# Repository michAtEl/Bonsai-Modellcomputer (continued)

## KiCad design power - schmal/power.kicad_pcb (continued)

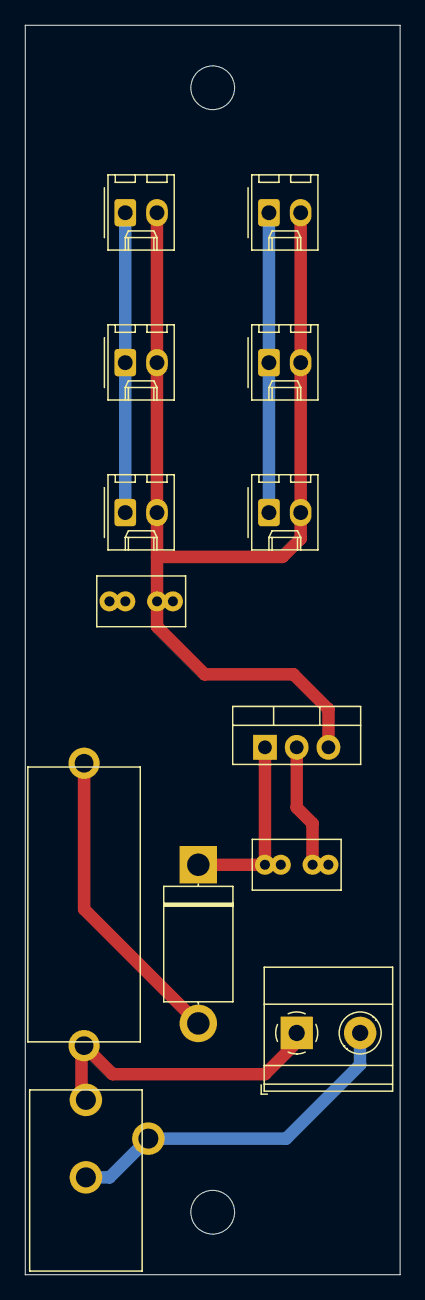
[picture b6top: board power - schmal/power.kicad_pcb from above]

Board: 2 copper layers, 30.0 x 100.0 mm, 15 parts (0 on the bottom side), 5 nets.

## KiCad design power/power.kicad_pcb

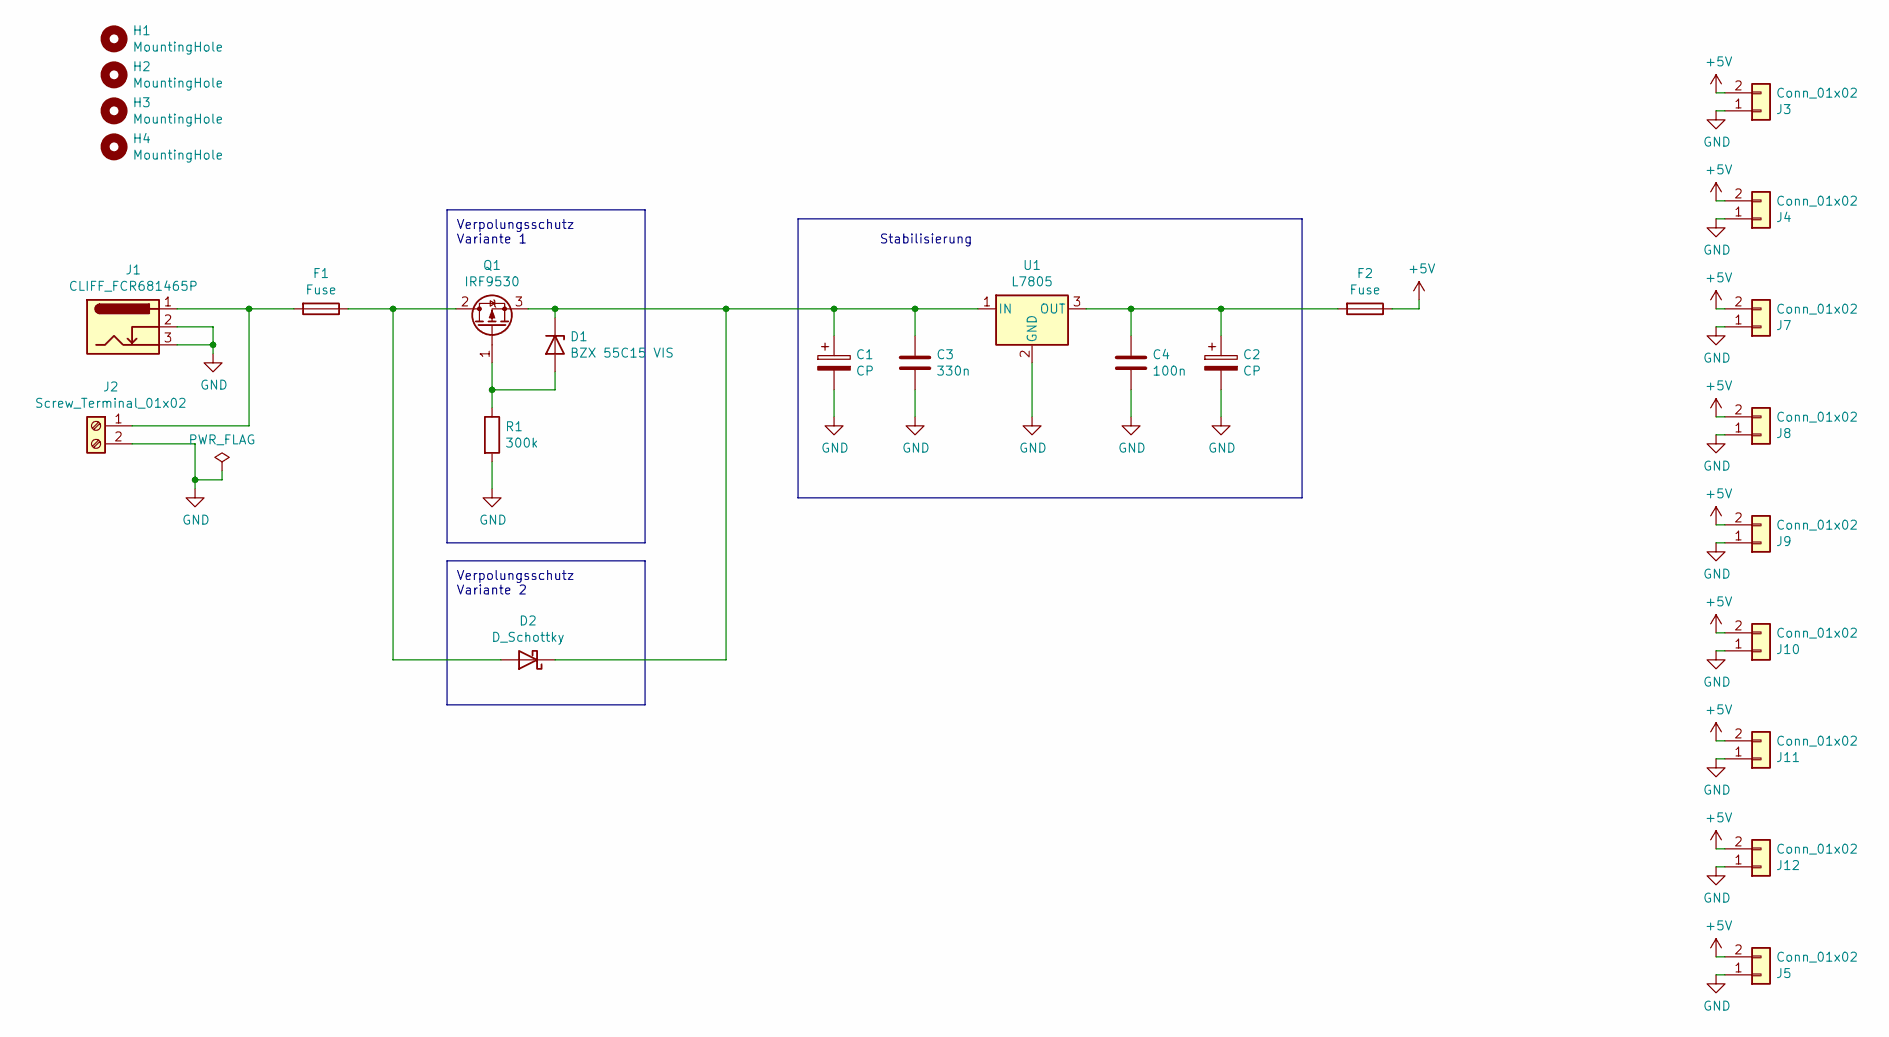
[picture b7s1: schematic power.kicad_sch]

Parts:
C1, C2: CP; CP_2.5_3.5_5
C3: 330n; C_Rect_L7.2mm_W2.2mm_P2.54mm_P5.08mm
C4: 100n; C_Rect_L7.2mm_W2.2mm_P2.54mm_P5.08mm
D1: BZX 55C15 VIS; D_T-1_P10.16mm_Horizontal
D2: D_Schottky; D_DO-201AE_P12.70mm_Horizontal
F1, F2: Fuse; Sicherungshalter
H1, H2, H3, H4: MountingHole; MountingHole_3.5mm
J1: CLIFF_FCR681465P
J2: Screw_Terminal_01x02; TerminalBlock_Phoenix_MKDS-1,5-2-5.08_1x02_P5.08mm_Horizont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
J3, J4, J5, J7, J8, J9, J10, J11, J12: Conn_01x02; Molex_KK-254_AE-6410-02A_1x02_P2.54mm_Vertical
Q1: IRF9530; TO-220-3_Vertical
R1: 300k; R_Axial_DIN0207_L6.3mm_D2.5mm_P10.16mm_Horizontal
U1: L7805; TO-220-3_Vertical

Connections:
+5V: F2.1, J3.2, J4.2, J5.2, J7.2, J8.2, J9.2, J10.2, J11.2, J12.2
GND: C1.2, C2.2, C3.2, C4.2, J1.2, J1.3, J2.2, J3.1, J4.1, J5.1, J7.1, J8.1, J9.1, J10.1, J11.1, J12.1, R1.2, U1.2 (GND)
unnamed: C1.1, C3.1, D1.1 (K), D2.1 (K), Q1.3 (S), U1.1 (IN)
unnamed: C2.1, C4.1, F2.2, U1.3 (OUT)
unnamed: D1.2 (A), Q1.1 (G), R1.1
unnamed: D2.2 (A), F1.1, Q1.2 (D)
unnamed: F1.2, J1.1, J2.1

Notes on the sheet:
Verpolungsschutz Variante 1
Verpolungsschutz Variante 2
Stabilisierung

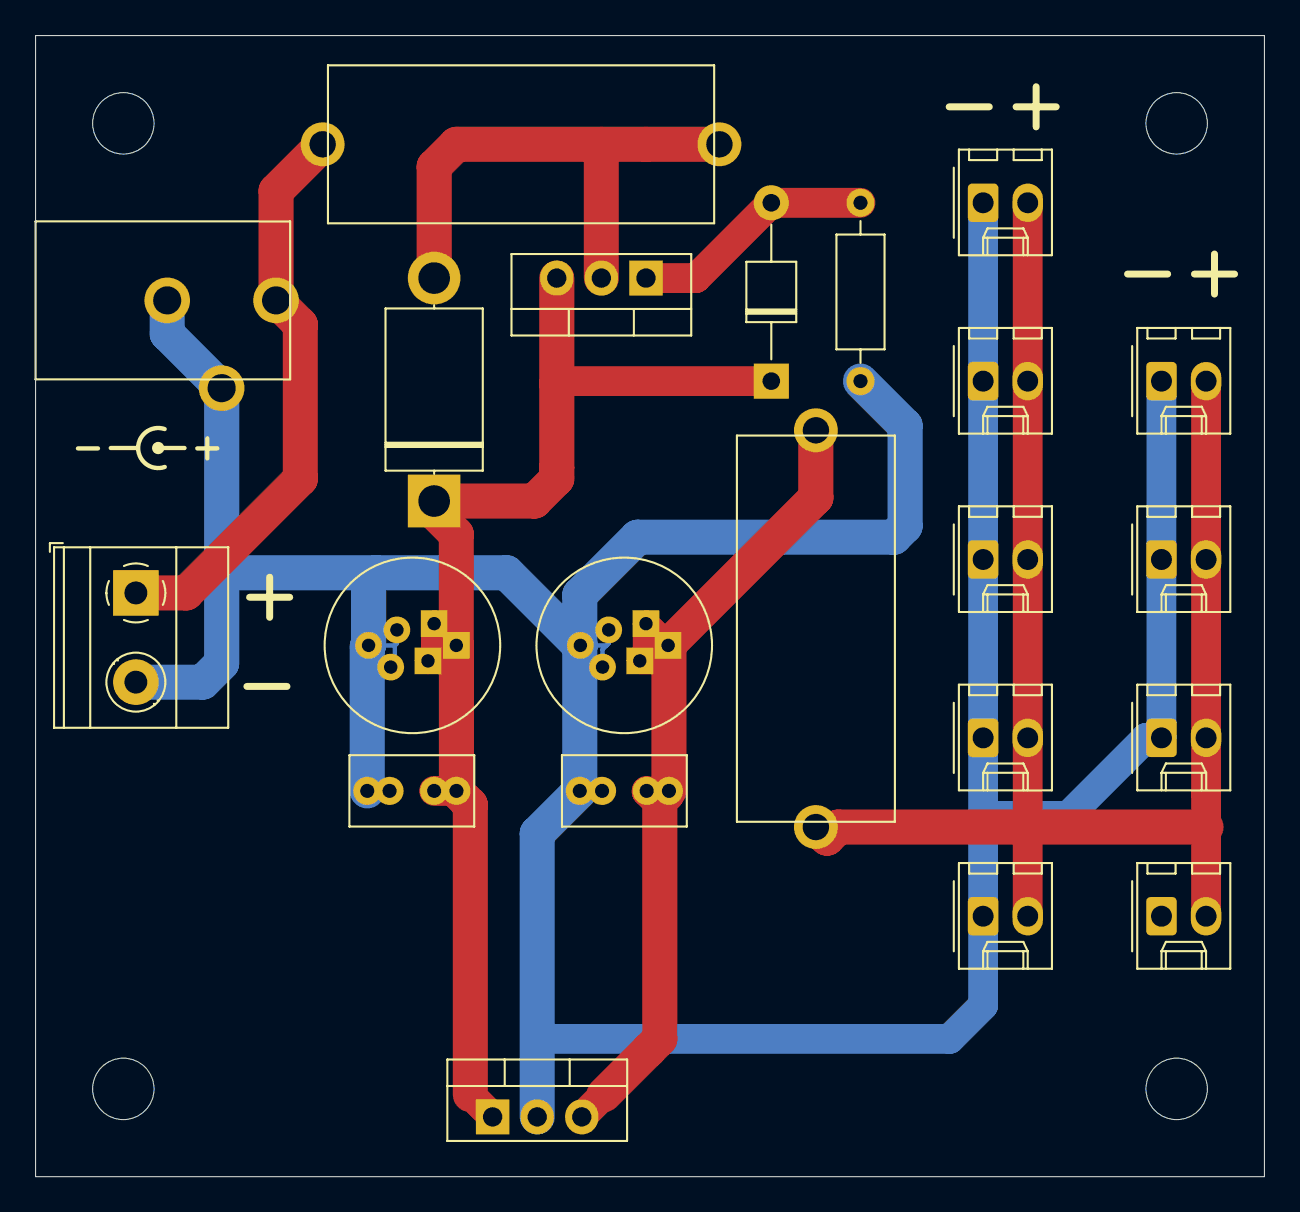
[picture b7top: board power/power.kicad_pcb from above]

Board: 2 copper layers, 70.0 x 65.0 mm, 26 parts (0 on the bottom side), 7 nets.

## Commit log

2020-10-15 Akku: Bauteilwerte ergänzt
2020-10-15 Akku: Schaltungen zum entprellen der Taster gleichartig angeordnet
2020-10-22 LEDs richtig rum gedreht
2020-10-24 redesign Steuerwerk angefangen
2020-10-24 vor Umbau 74541 im Schaltplan
2020-10-24 Steuerwerk: beide 74541 umgebaut
2020-10-24 Steuerwerk vor Entfernen der Busse
2020-10-24 weitergemacht
2020-10-25 Steuerwerk weitergemacht
2020-10-25 Steuerwerk fertig außer Diodenmatrix
2020-10-25 Steuerwerk fast fertig TODO: Beschriftung überarbeiten
2020-10-26 Steuerwerk: - Sperrbereiche für die Köpfe der Befestigungsschrauben hinzugefügt - Beschriftung (Silkscreen) auf der Platinenoberseite bearbeitet
2020-10-28 viele Kleinigkeiten
2020-10-30 Steuerwerk: Verbinder für die beiden unbenutzten Steuersignale eingebaut
2020-10-30 Steuerwerk: Platzhalter für LEDs eingefügt
2020-10-30 Line Width im Silkscreen an die Vorgaben con jlcpcb angepasst
2020-10-30 Steuerwerk: weitere Platzhalterdioden eingebaut
2020-10-31 Steuerwerk: Linien im Silkscreen in den Footprints der LEDs in der Diodenmatrix entfernt
2020-10-31 Steuerwerk: alle Diodenplatzhalter eingebaut
2020-10-31 Steuerwerk: EdgeCuts verschoben
2020-10-31 Steuerwerk rev 2.0
2020-10-31 Befehle: vor Umbau der Diodenmatrix im Schalplan
2020-10-31 Befehle: Schaltplan bearbeitet
2020-11-01 Befehle: Schaltplan geändert
2020-11-05 Steuerwerk und Befehle bearbeitet
2020-11-06 Footprint EuroBoard gedreht und auf das Gitter gelegt (Ursprung links oben)
2020-11-06 Befehle: An der Platine weitergearbeitet
2020-11-07 Befehle: Platine fertig (TODO: Kontrolle)
2020-11-07 Backup vor Umbennung von Netzen
2020-11-07 Akku/PC: Schaltplan mit Bussen gezeichnet; Netze der Busse sinnvoll benannt
2020-11-07 Akku/PC: Schaltplan aufgeräumt
2020-11-08 Steuerwerk: keine verstecken Pins mehr; alle Pins explizit im Schaltplan angeschossen
2020-11-08 Befehle: alle versteckten Pins durch sichtbare Pins ersetzt; VCC und GND an jedem IC explizit im Schaltplan angeschlossen.
2020-11-15 Steuerwerk 2.0 gerber exportiert
2020-11-15 Befehle und Steuerwerk: - Kleinkram - gerber rev 2.0 für Bestellung exportiert
2020-11-15 Kleinigkeiten
2020-11-29 Akku weitergebaut
2020-12-04 Bauteilwerte in Benutzerebene angezeigt
2020-12-18 Akku/PC Layout angefangen
2020-12-18 Akku Board weiter
2020-12-18 Akku Layout weitergemacht
2020-12-18 Speichermodul weitergebaut
2020-12-19 Speicher weitergebaut
2020-12-20 Speicher Layout EinTaktReset VCO
2020-12-20 Speicher vor Tausch der Taster
2020-12-20 Speicher fertig*
2020-12-21 EinTaktReset
2020-12-22 Akku, Speicher, EinTaktReset: Via-Durchmesser vergrößert
2020-12-23 viele kleine Änderungen
2020-12-23 Netze umbenannt
2020-12-23 EinTaktReset kleine Korrekturen
2021-01-25 viel Kleinkram
2021-08-01 Revision auf allen Schaltplänen eingetragen
2021-10-11 Readme angepasst
2021-10-11 Bild hinzugefügt
2021-10-12 Readme angepasst Kabelhalter eingefügt
2021-10-12 Verdrahtung.svg hinzugefügt
2023-05-30 Kabelhalter: STL-Dateien hinzugefügt
2023-06-05 Verdrahtung geändert, Bild ausgetauscht
2024-03-11 - alles auf KiCad 7 umgestellt - EinTaktReset neu (mit Mikrocontroller)
2024-03-11 - Werte von Bauteilen in den Schaltplänen ergänzt - weitere Hinweise zum Nachbau
2024-08-11 schmale Platine für die Spannungsversorgung
2024-08-11 Alle Vorwiderstände vor LEDs in 680 Ohm geändert (Issue 5)
2024-09-14 weitere Hinweise zum Nachbau
